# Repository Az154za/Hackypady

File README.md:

# Hackypady

Hackypady is a 9 key keyboard with one 0.91" OLED dispaly , 1 rotatory encoder , 3 multicolor LEDs (RGB) it does contain the XIAO seeed RP 2040 its objectif is to make u have fast access to ur favourite apps , shortcuts ....

##PCB
Here is my PCB with the schematic .it's made in Kicad .in This case I did the simple rotatory encoder because I have no pins digital pins  

## Assembly
1. Mount the OLED and encoder where visible/easy to reach.
2. Arrange the 9 switches in your preferred layout (3×3 grid is common).
3. Wire the switches into a diode matrix (each switch in series with a diode) to allow scanning with fewer pins.
4. Connect the encoder and OLED to the RP2040 according to the pinout you plan to use.
5. Double-check power (3.3V) and ground connections before powering.

## Firmware / Software
The firmware is made with KMK python to set up the initiation of buttons and the encoder up and down volume 

## About this project
This project is highly scalable and depends on what micro controller you want to use or what's ur idea 

## Bill of Materials 
- 1 × Seeed XIAO RP2040 (or compatible RP2040 board)
- 1 × 0.91" OLED (I2C, 128×32 or 128×64)
- 1 × Rotary encoder switch or not ( it's an option)
- 9 × push buttons
- 9 × diodes (1N4148) for matrix design

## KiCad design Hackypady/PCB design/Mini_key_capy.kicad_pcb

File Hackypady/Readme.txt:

This project is consisted of a mini keyboard that allows use to execute an app , web even external things … 
it is composed of OLED display 0.91" , a rotatory encoder , 9 switches mounted in matrix ( 6 total pins ) and the XIAO RP2040
this project is totally customisable scalable 
be free to grab this project and study it yourself .

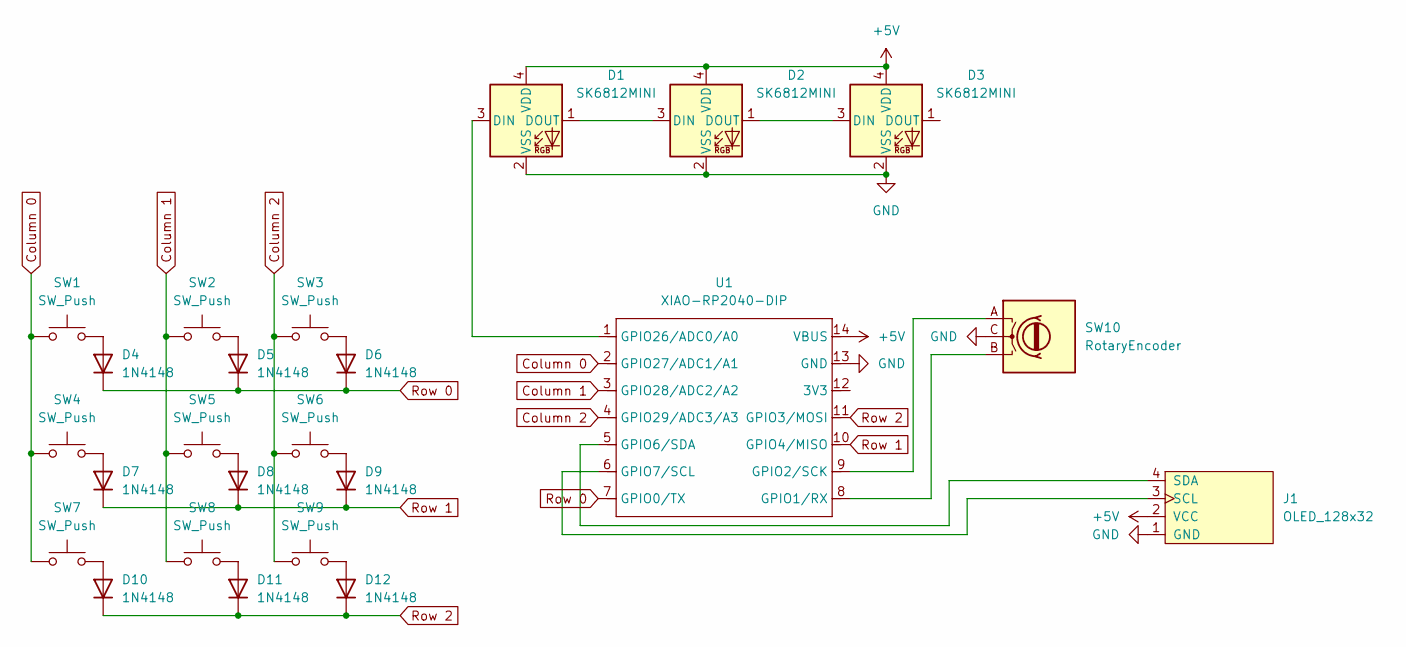
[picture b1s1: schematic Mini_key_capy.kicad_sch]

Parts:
D1, D2, D3: SK6812MINI; LED_SK6812MINI_PLCC4_3.5x3.5mm_P1.75mm
D4, D5, D6, D7, D8, D9, D10, D11, D12: 1N4148; D_DO-35_SOD27_P7.62mm_Horizontal
J1: OLED_128x32; SSD1306-0.91-OLED-4pin-128x32 (2)
SW1, SW2, SW3, SW4, SW5, SW6, SW7, SW8, SW9: SW_Push; SW_Cherry_MX_1.00u_PCB
SW10: RotaryEncoder; RotaryEncoder_Alps_EC11E_Vertical_H20mm
U1: XIAO-RP2040-DIP

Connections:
+5V: D1.4 (VDD), D2.4 (VDD), D3.4 (VDD), J1.2 (VCC), U1.14 (VBUS)
Column 0: SW1.1, SW4.1, SW7.1, U1.2 (GPIO27/ADC1/A1)
Column 1: SW2.1, SW5.1, SW8.1, U1.3 (GPIO28/ADC2/A2)
Column 2: SW3.1, SW6.1, SW9.1, U1.4 (GPIO29/ADC3/A3)
GND: D1.2 (VSS), D2.2 (VSS), D3.2 (VSS), J1.1 (GND), SW10.C, U1.13 (GND)
unnamed: D1.3 (DIN), U1.1 (GPIO26/ADC0/A0)
unnamed: D1.1 (DOUT), D2.3 (DIN)
unnamed: D2.1 (DOUT), D3.3 (DIN)
unnamed: D4.2 (A), SW1.2
unnamed: D5.2 (A), SW2.2
unnamed: D6.2 (A), SW3.2
unnamed: D7.2 (A), SW4.2
unnamed: D8.2 (A), SW5.2
unnamed: D9.2 (A), SW6.2
unnamed: D10.2 (A), SW7.2
unnamed: D11.2 (A), SW8.2
unnamed: D12.2 (A), SW9.2
unnamed: J1.3 (SCL), U1.6 (GPIO7/SCL)
unnamed: J1.4 (SDA), U1.5 (GPIO6/SDA)
unnamed: SW10.B, U1.8 (GPIO1/RX)
unnamed: SW10.A, U1.9 (GPIO2/SCK)
Row 0: D4.1 (K), D5.1 (K), D6.1 (K), U1.7 (GPIO0/TX)
Row 1: D7.1 (K), D8.1 (K), D9.1 (K), U1.10 (GPIO4/MISO)
Row 2: D10.1 (K), D11.1 (K), D12.1 (K), U1.11 (GPIO3/MOSI)

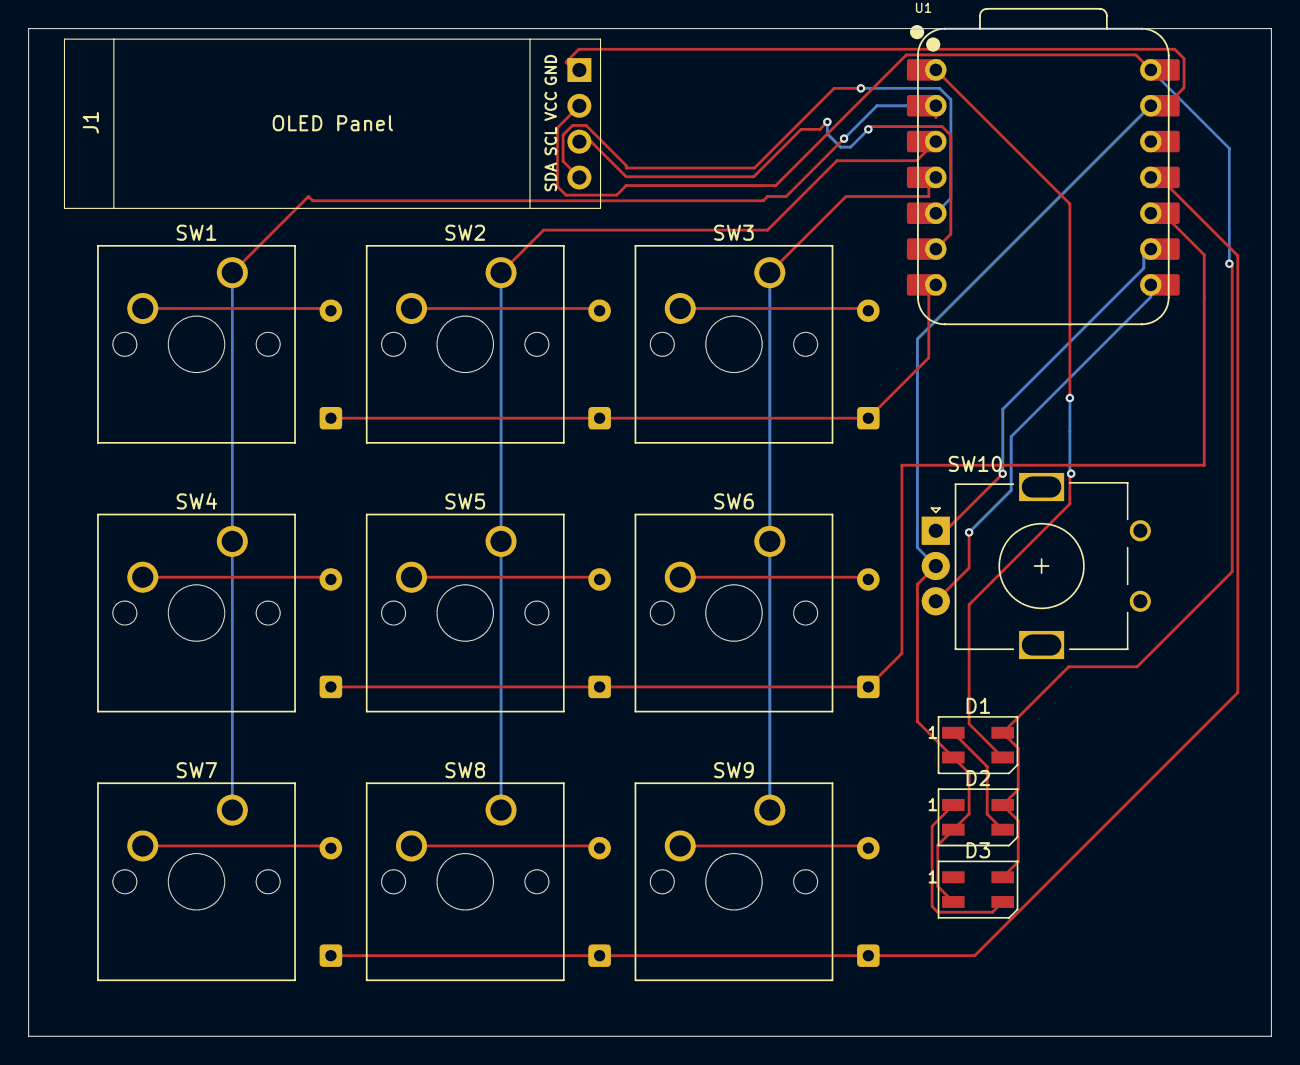
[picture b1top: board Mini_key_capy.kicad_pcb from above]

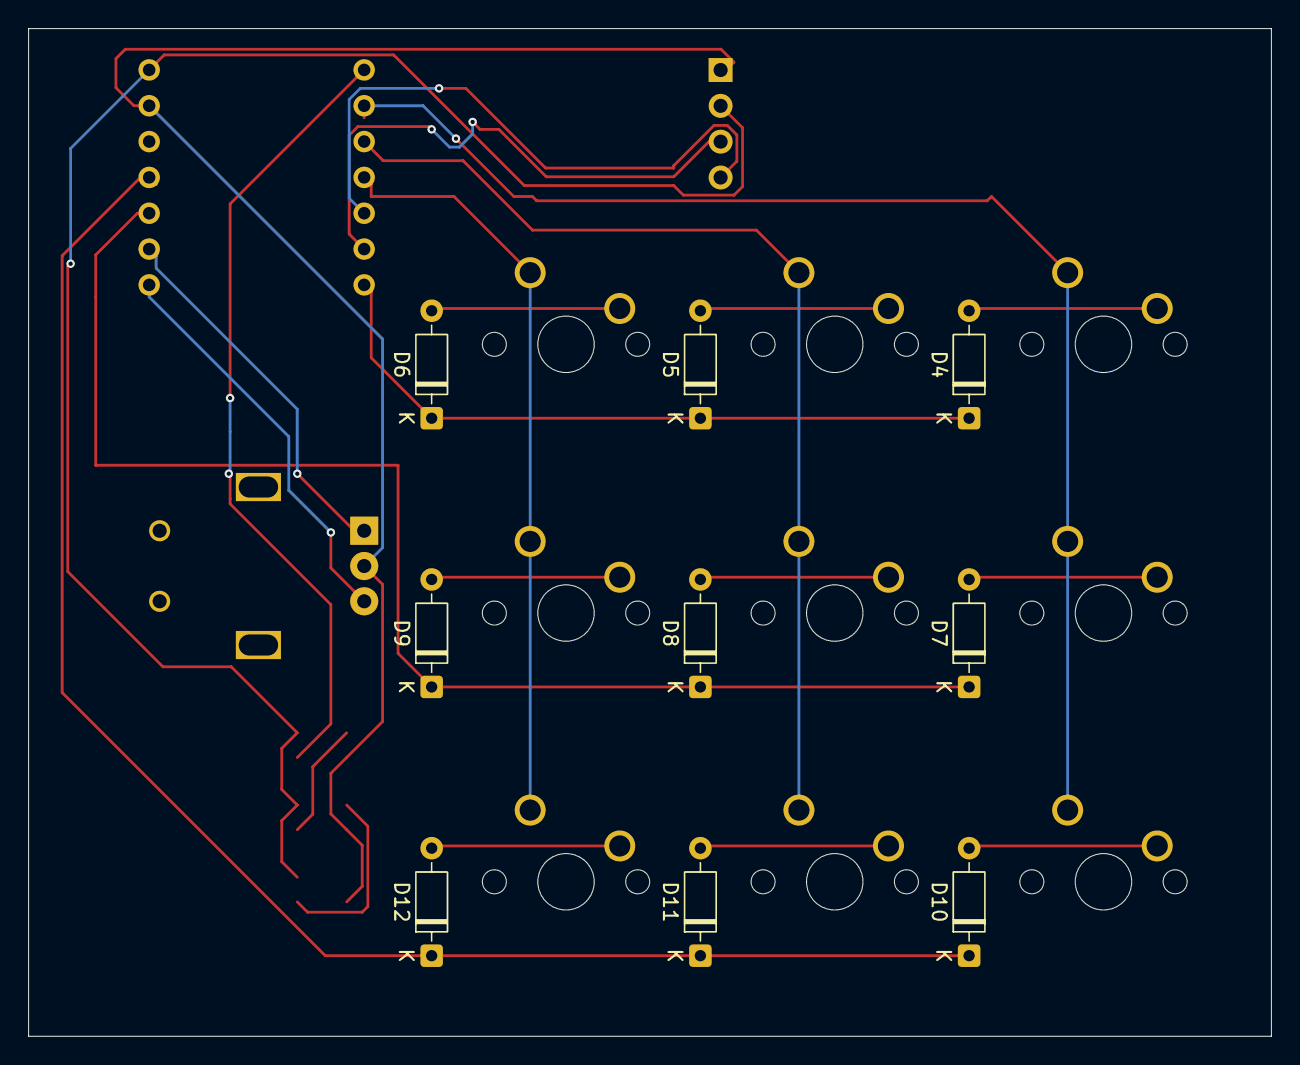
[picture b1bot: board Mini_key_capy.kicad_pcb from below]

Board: 2 copper layers, 88.1 x 71.4 mm, 24 parts (9 on the bottom side), 24 nets.

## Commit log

2025-12-11 Initial plan
2025-12-11 Enhance README with project details and components
    Added project description and details about components.
2025-12-11 Add comprehensive documentation and project structure to make Hackypady impressive
2025-12-11 Revise README.md for clarity and detail
    Expanded project description and added detailed sections on features, assembly, firmware, customization, troubleshooting, contributing, roadmap, and credits.
2025-12-11 Fix QMK deprecation warnings and improve code quality
2025-12-11 Add Quick Start guide and comprehensive Showcase documentation
2025-12-11 Fix typo in IssueHunt username field
2025-12-11 Program
    Implement XIAO RP2040 Keyboard Controller with button matrix, rotary encoder, RGB LEDs, and OLED display.
2025-12-11 Add LICENSE, CONTRIBUTING, CODE_OF_CONDUCT and GitHub templates
2025-12-11 Add comprehensive documentation: FAQ, Quick Start, Project Structure, Changelog, and .gitignore
2025-12-11 Address code review feedback: remove hard-coded line numbers and improve documentation clarity
2025-12-11 Update README with comprehensive improvements
2025-12-11 Fix GPIO pin count in README description
2025-12-11 Improve pinout terminology consistency and library references
2025-12-11 Enhance README with improved structure, emojis, and detailed sections
2025-12-11 Update README to reflect KMK/CircuitPython firmware instead of Arduino C++
2025-12-11 Clarify KMK installation steps and XIAO RP2040 pin naming
2025-12-11 Add legacy firmware to repo contents and improve KMK pin configuration examples
2025-12-11 Improve Quick Start wording for CircuitPython installation
2025-12-12 Add image to README for visual reference
    Added an image to the README for visual reference.
2025-12-12 Update README with project description and features
2025-12-12 Improve README with project details and assembly steps
    Updated README.md to enhance project description and assembly instructions.
2025-12-12 Fix formatting and update README header
2025-12-12 Update README with firmware implementation details
    Clarify firmware choice and mention KMK library usage.
2025-12-13 Revise README with updated BOM and assembly instructions
    Updated the Bill of Materials and Assembly sections with additional images and details.
2025-12-16 Add MIT LICENSE file
2025-12-16 Update LICENSE to Personal Use - non-commercial, no sharing
